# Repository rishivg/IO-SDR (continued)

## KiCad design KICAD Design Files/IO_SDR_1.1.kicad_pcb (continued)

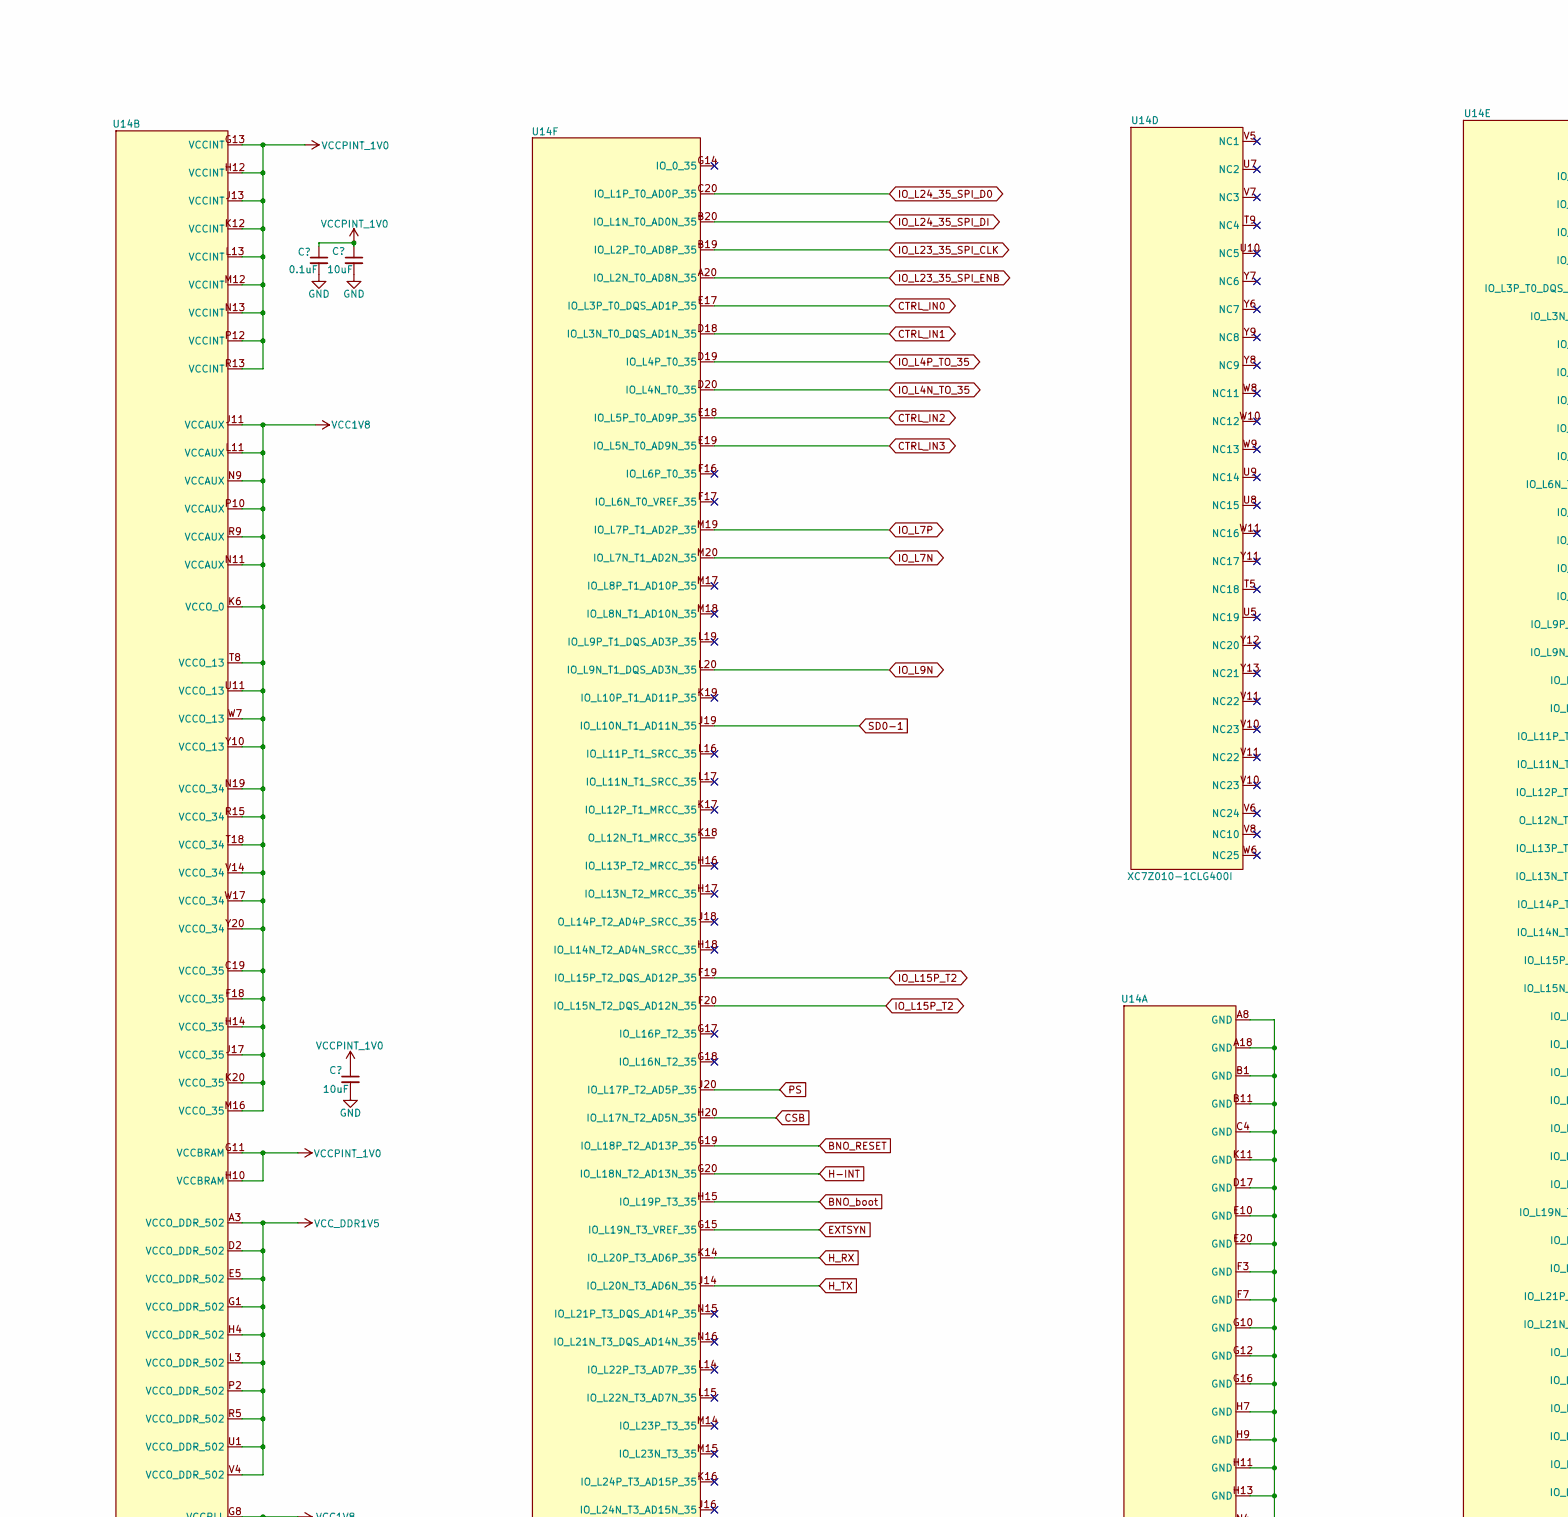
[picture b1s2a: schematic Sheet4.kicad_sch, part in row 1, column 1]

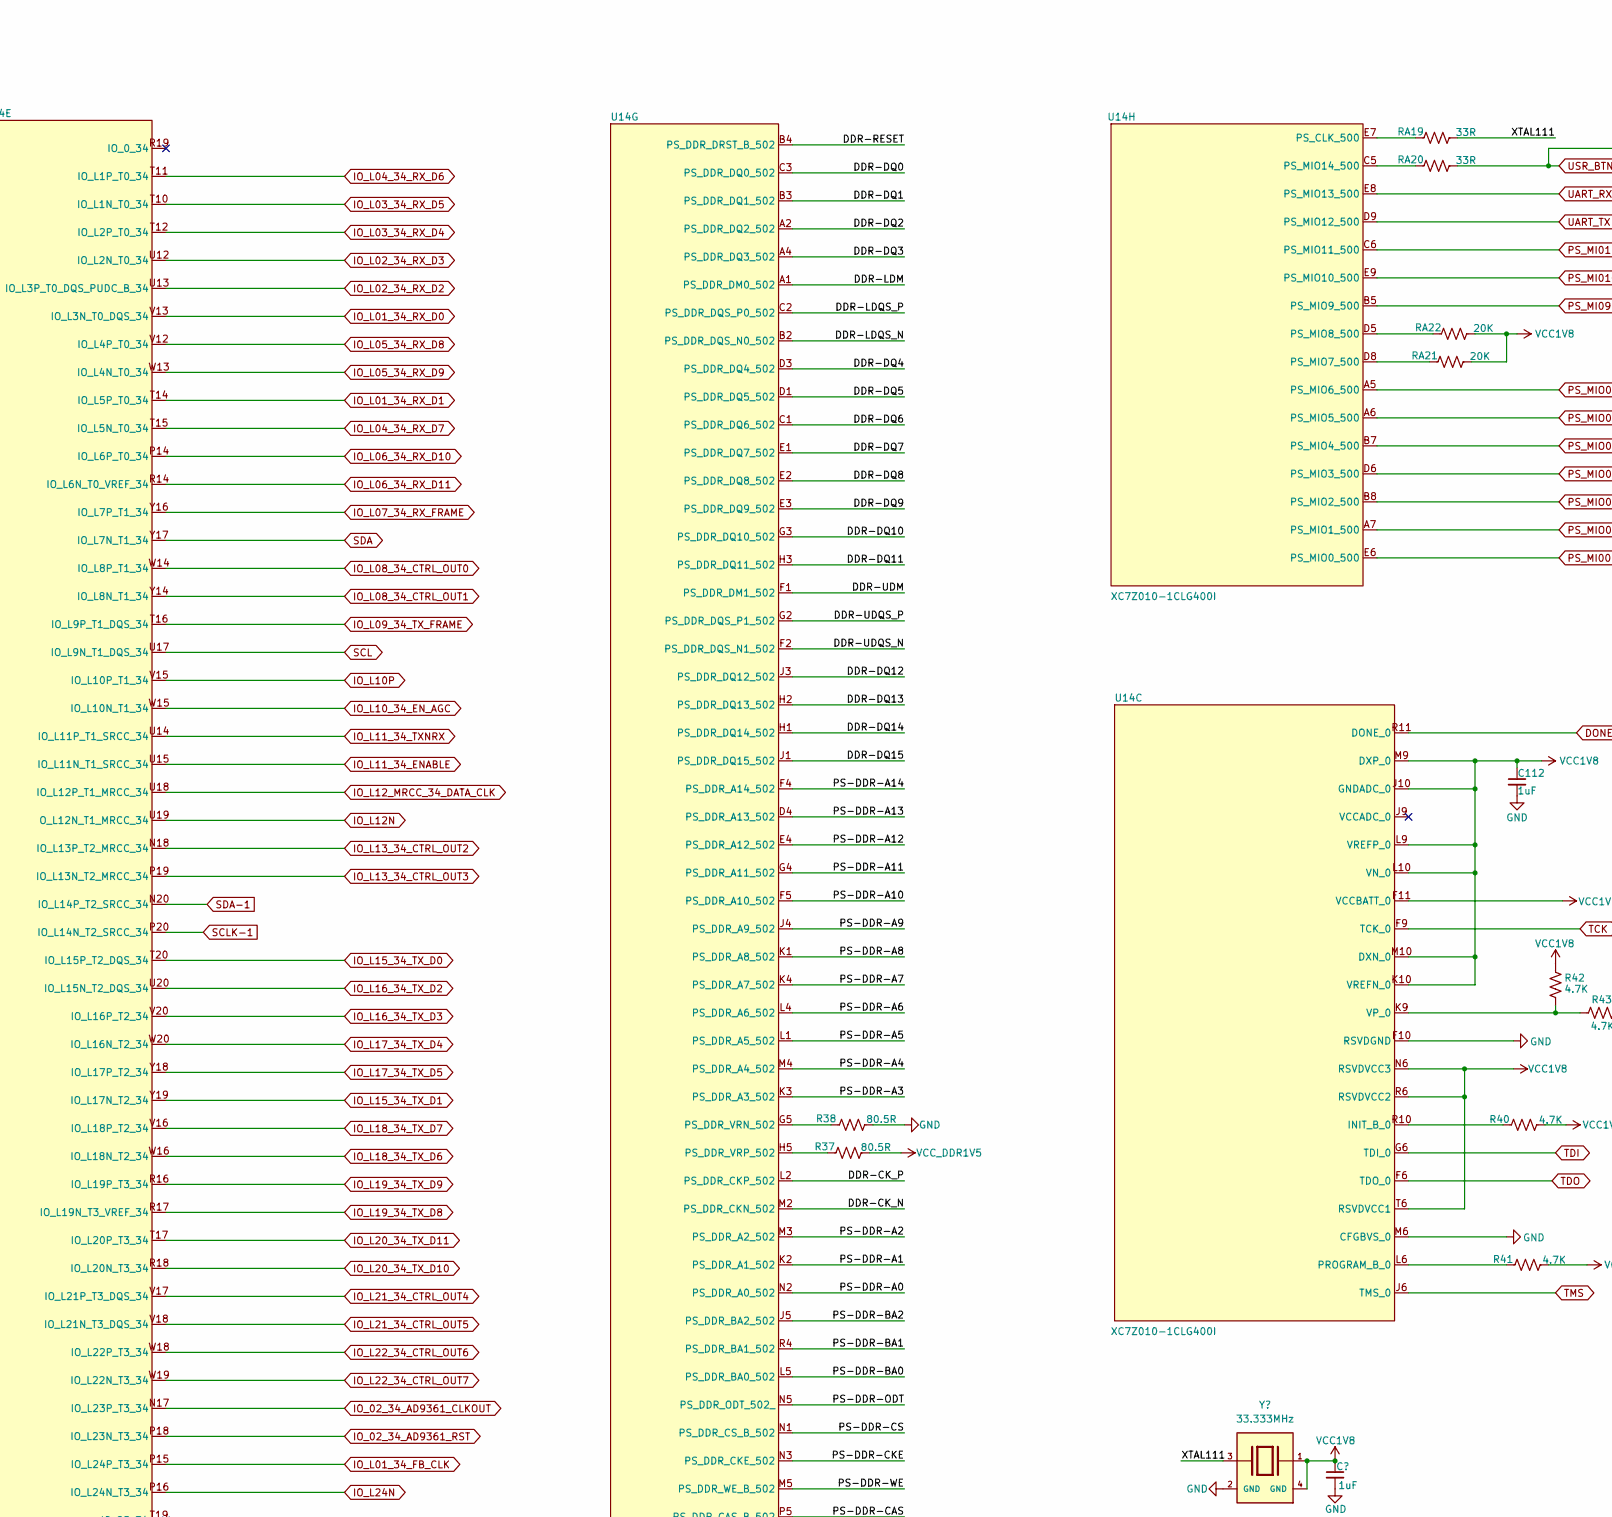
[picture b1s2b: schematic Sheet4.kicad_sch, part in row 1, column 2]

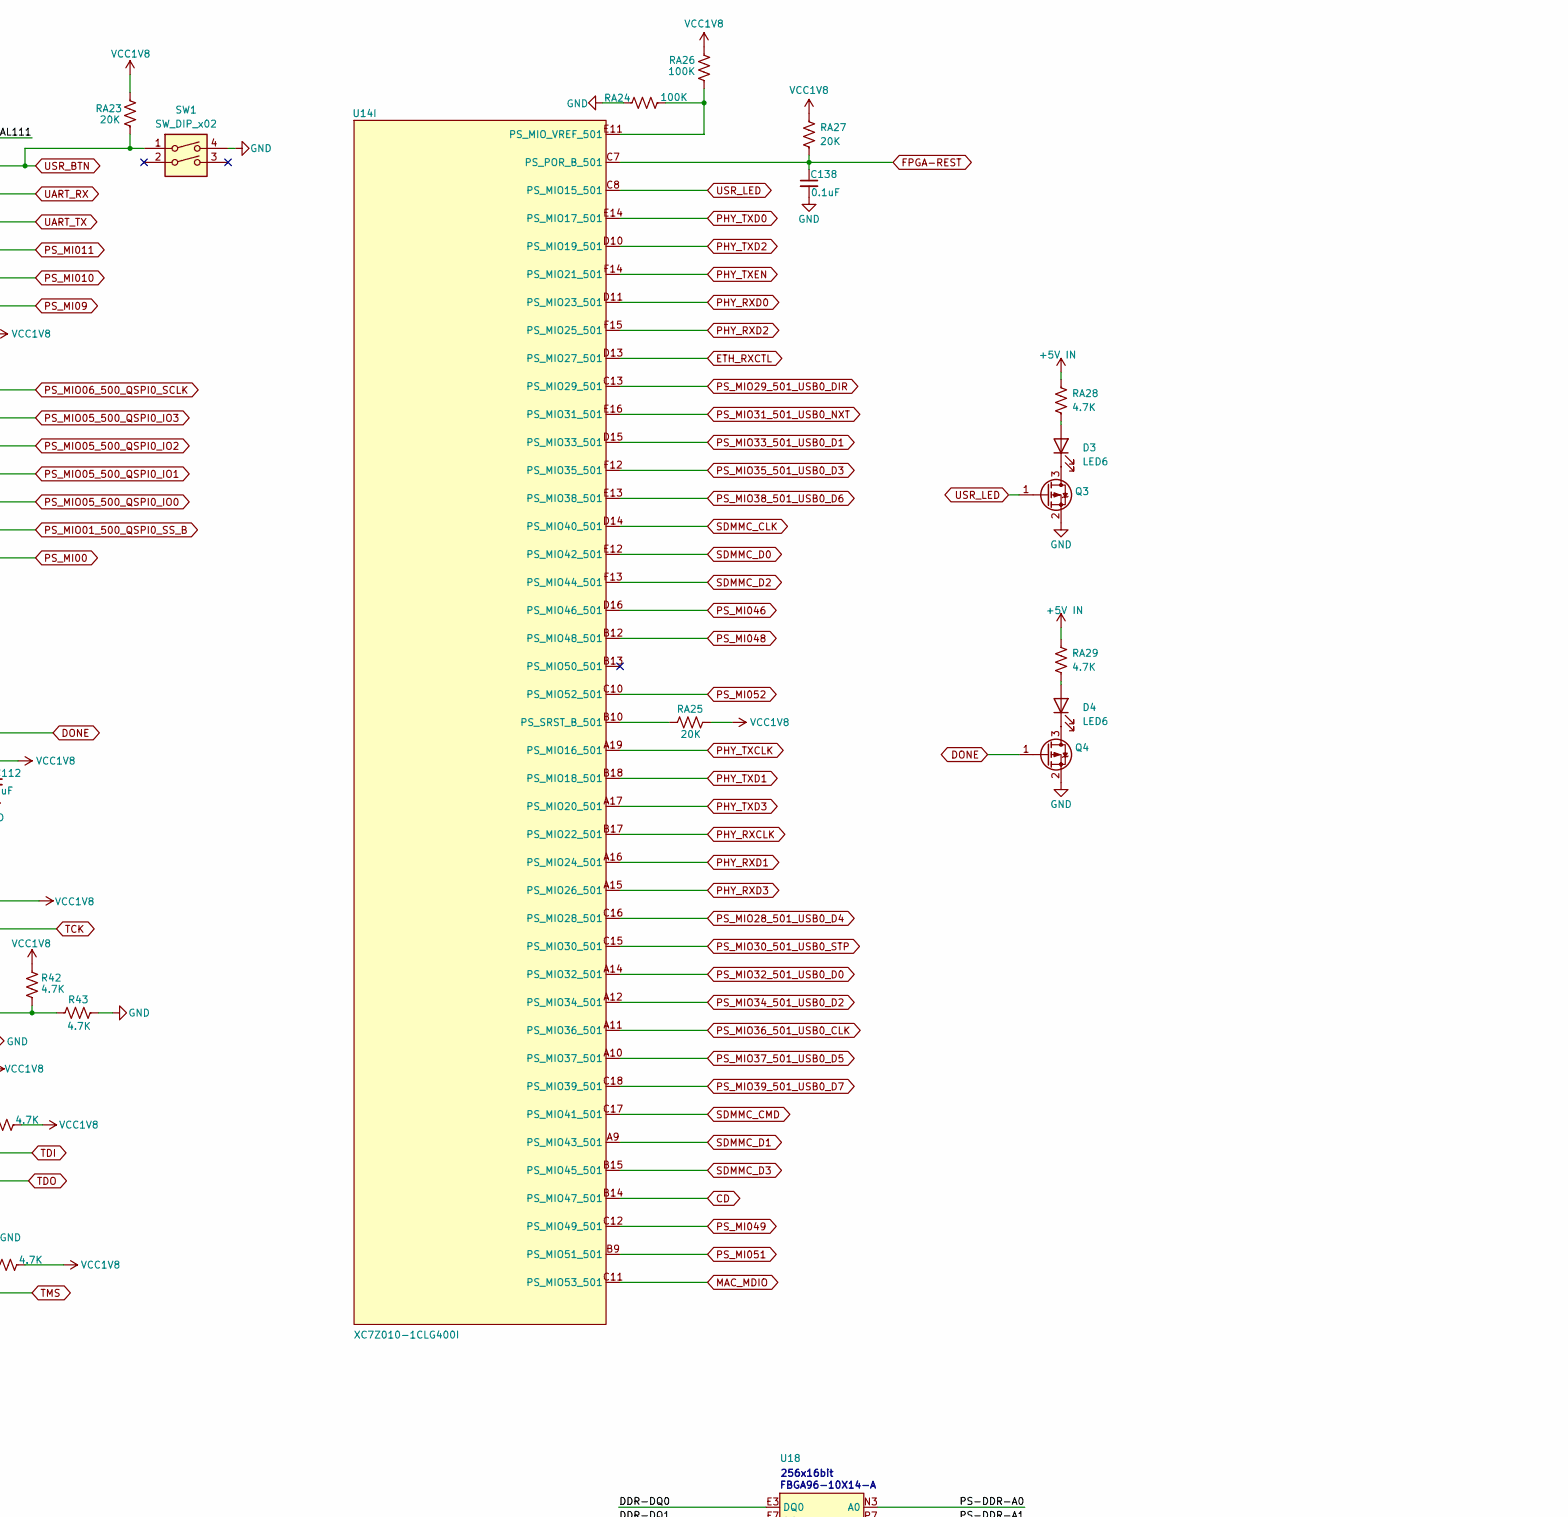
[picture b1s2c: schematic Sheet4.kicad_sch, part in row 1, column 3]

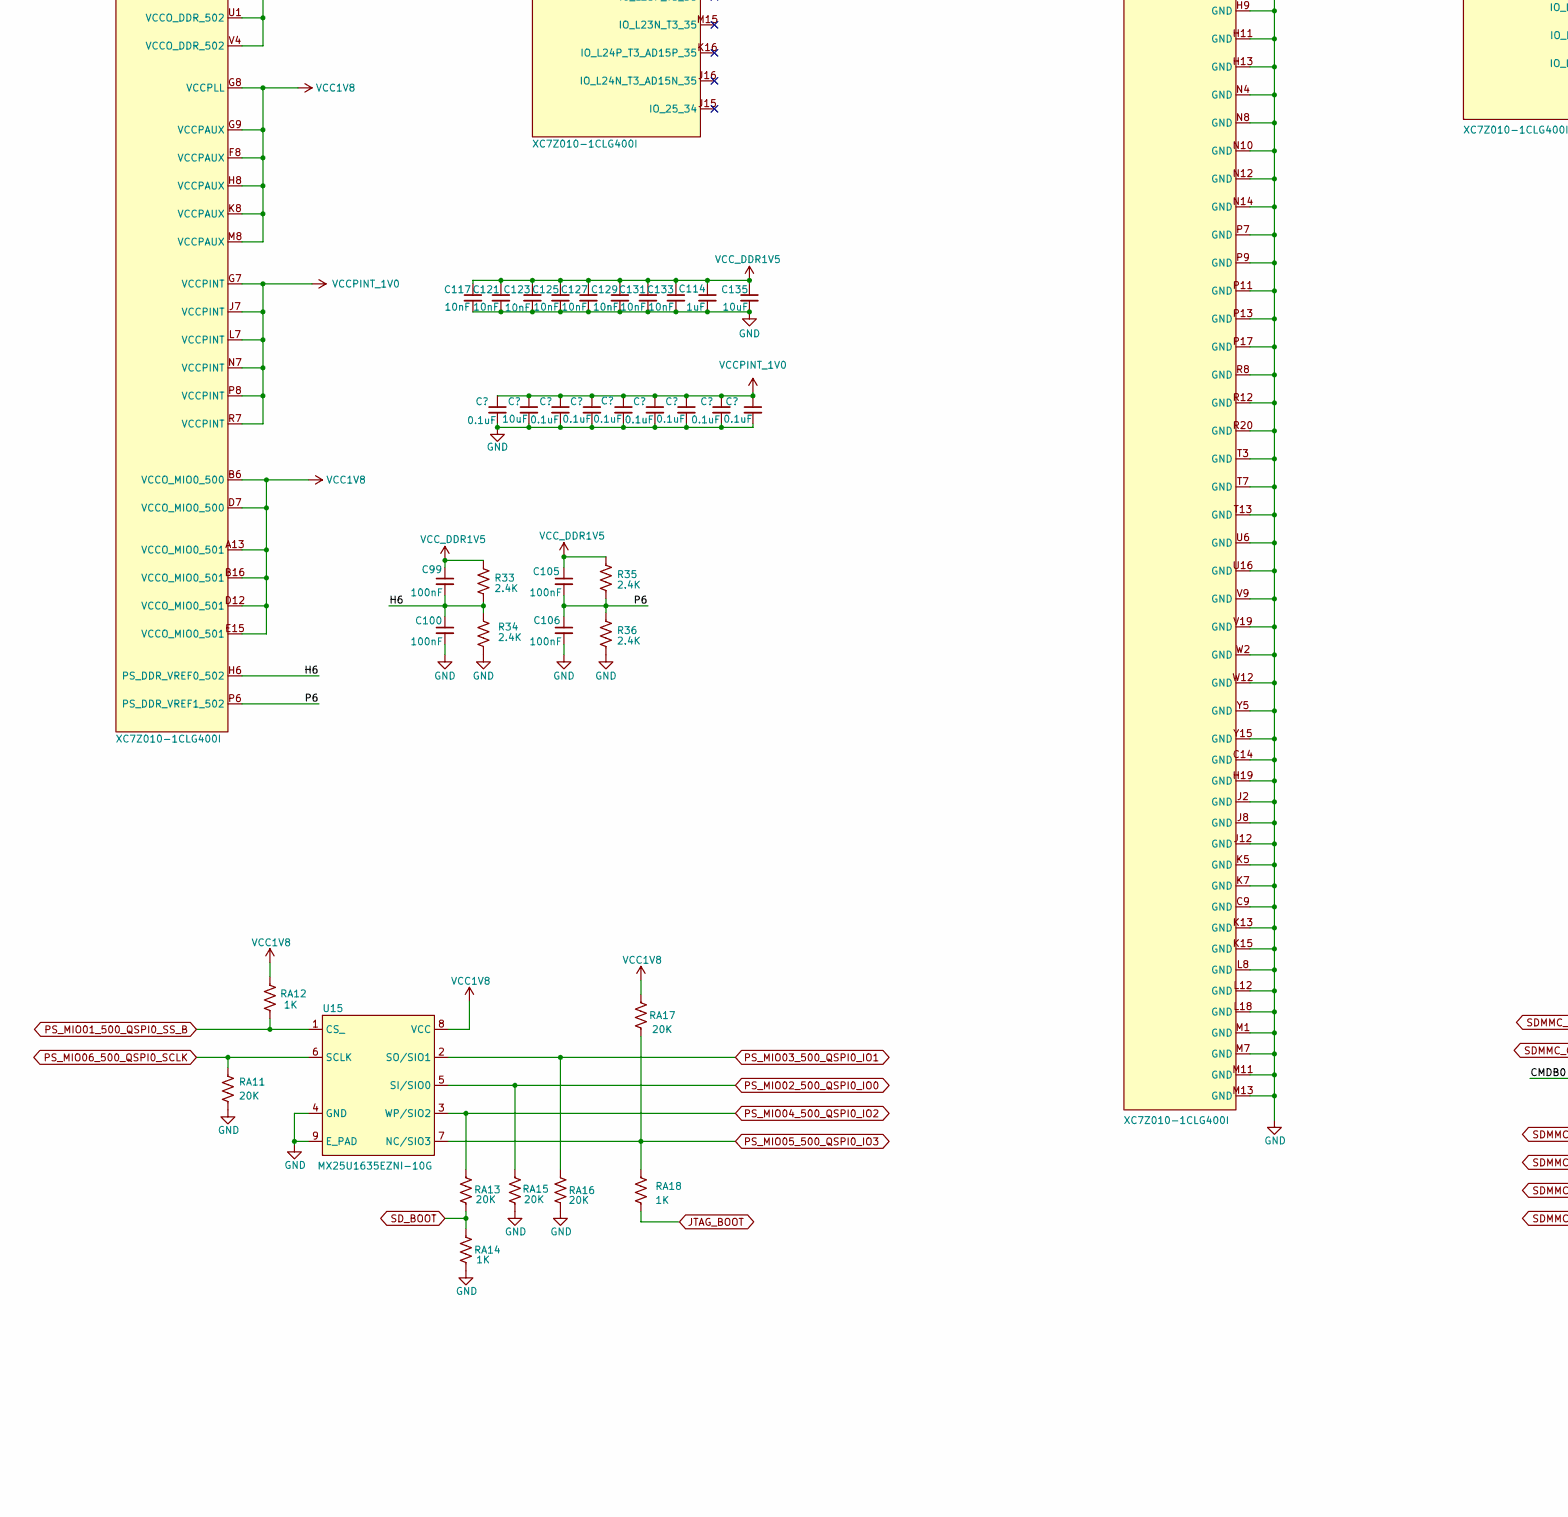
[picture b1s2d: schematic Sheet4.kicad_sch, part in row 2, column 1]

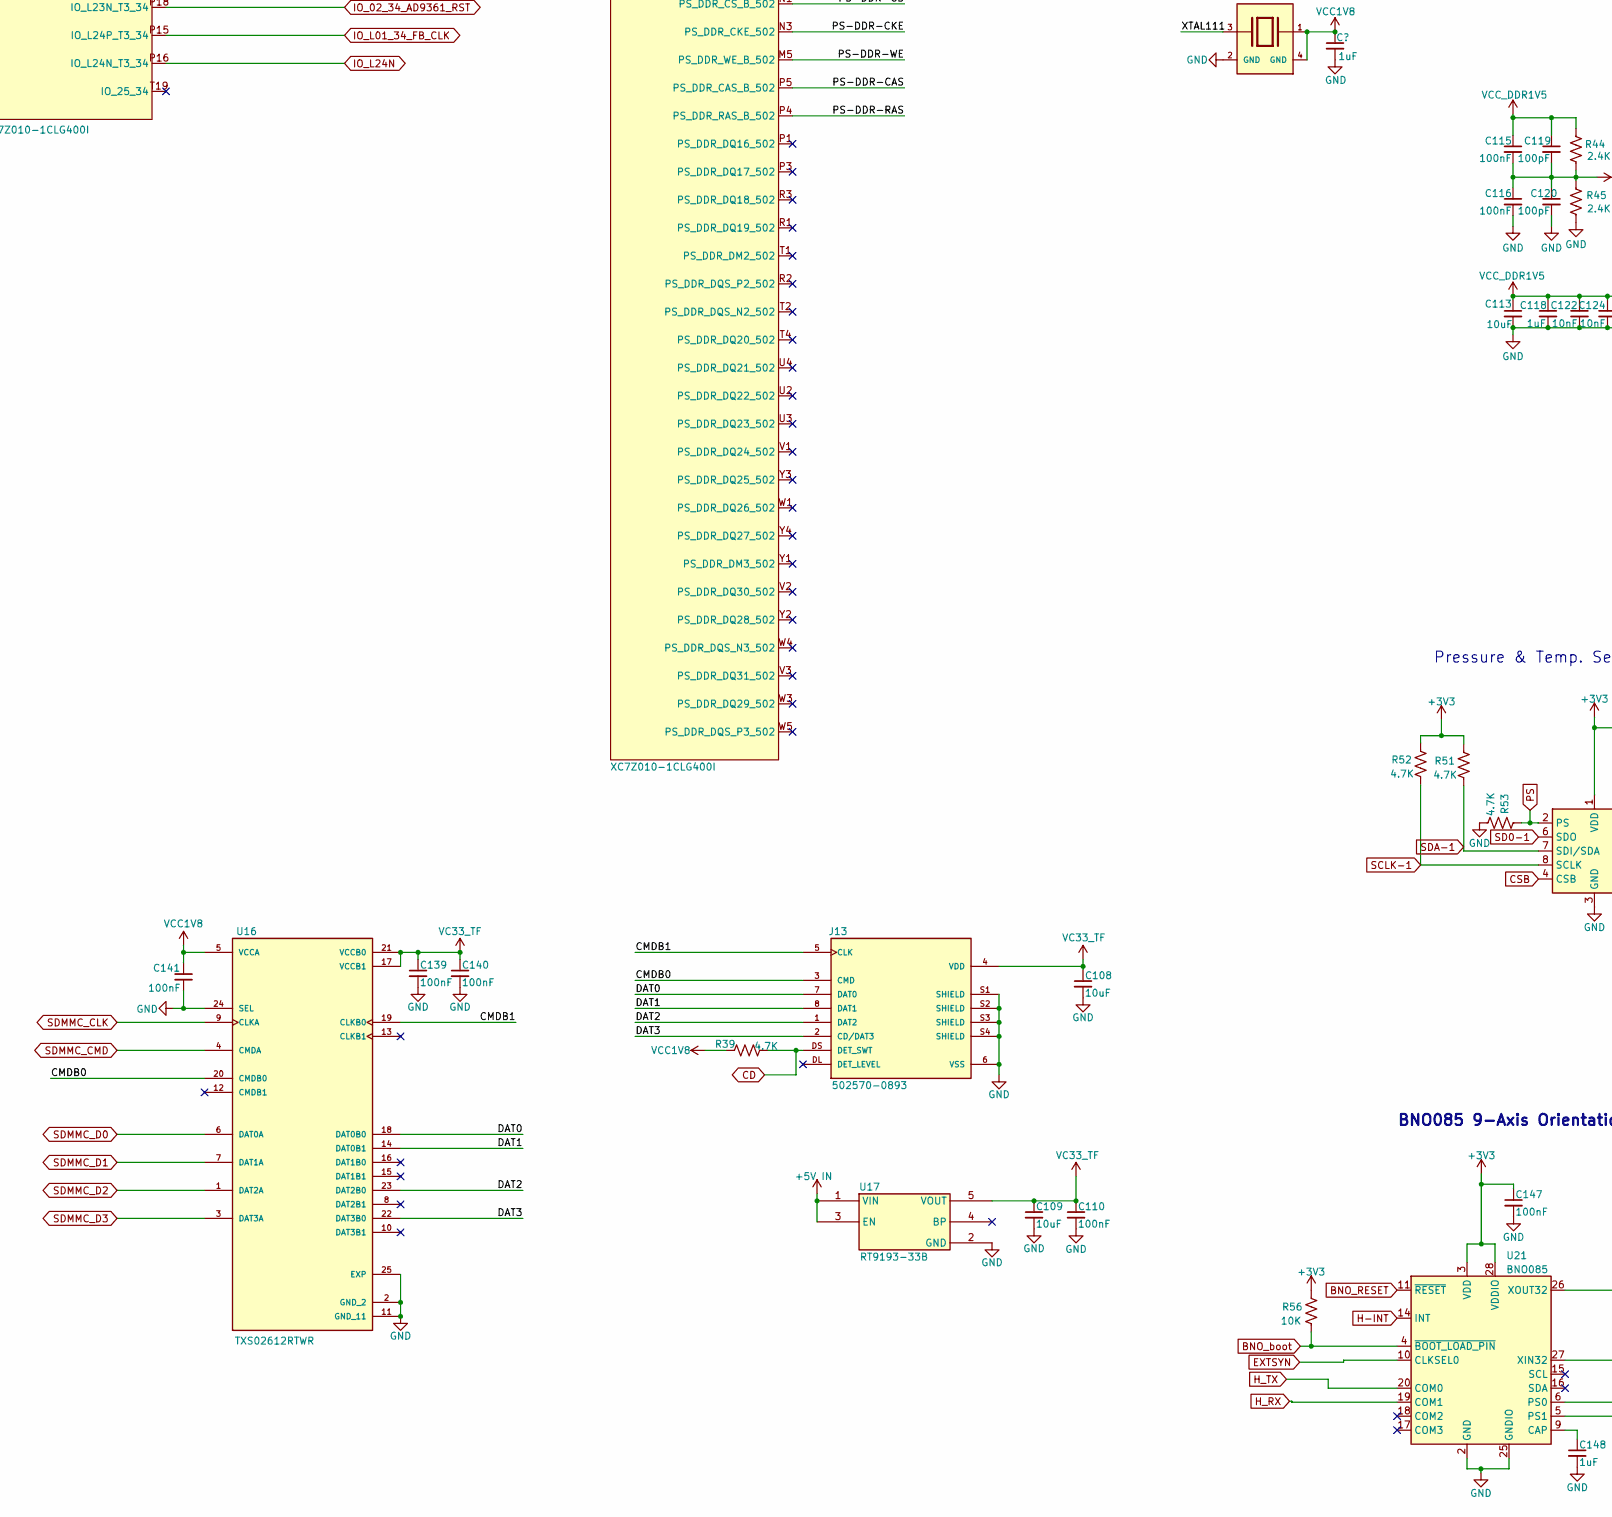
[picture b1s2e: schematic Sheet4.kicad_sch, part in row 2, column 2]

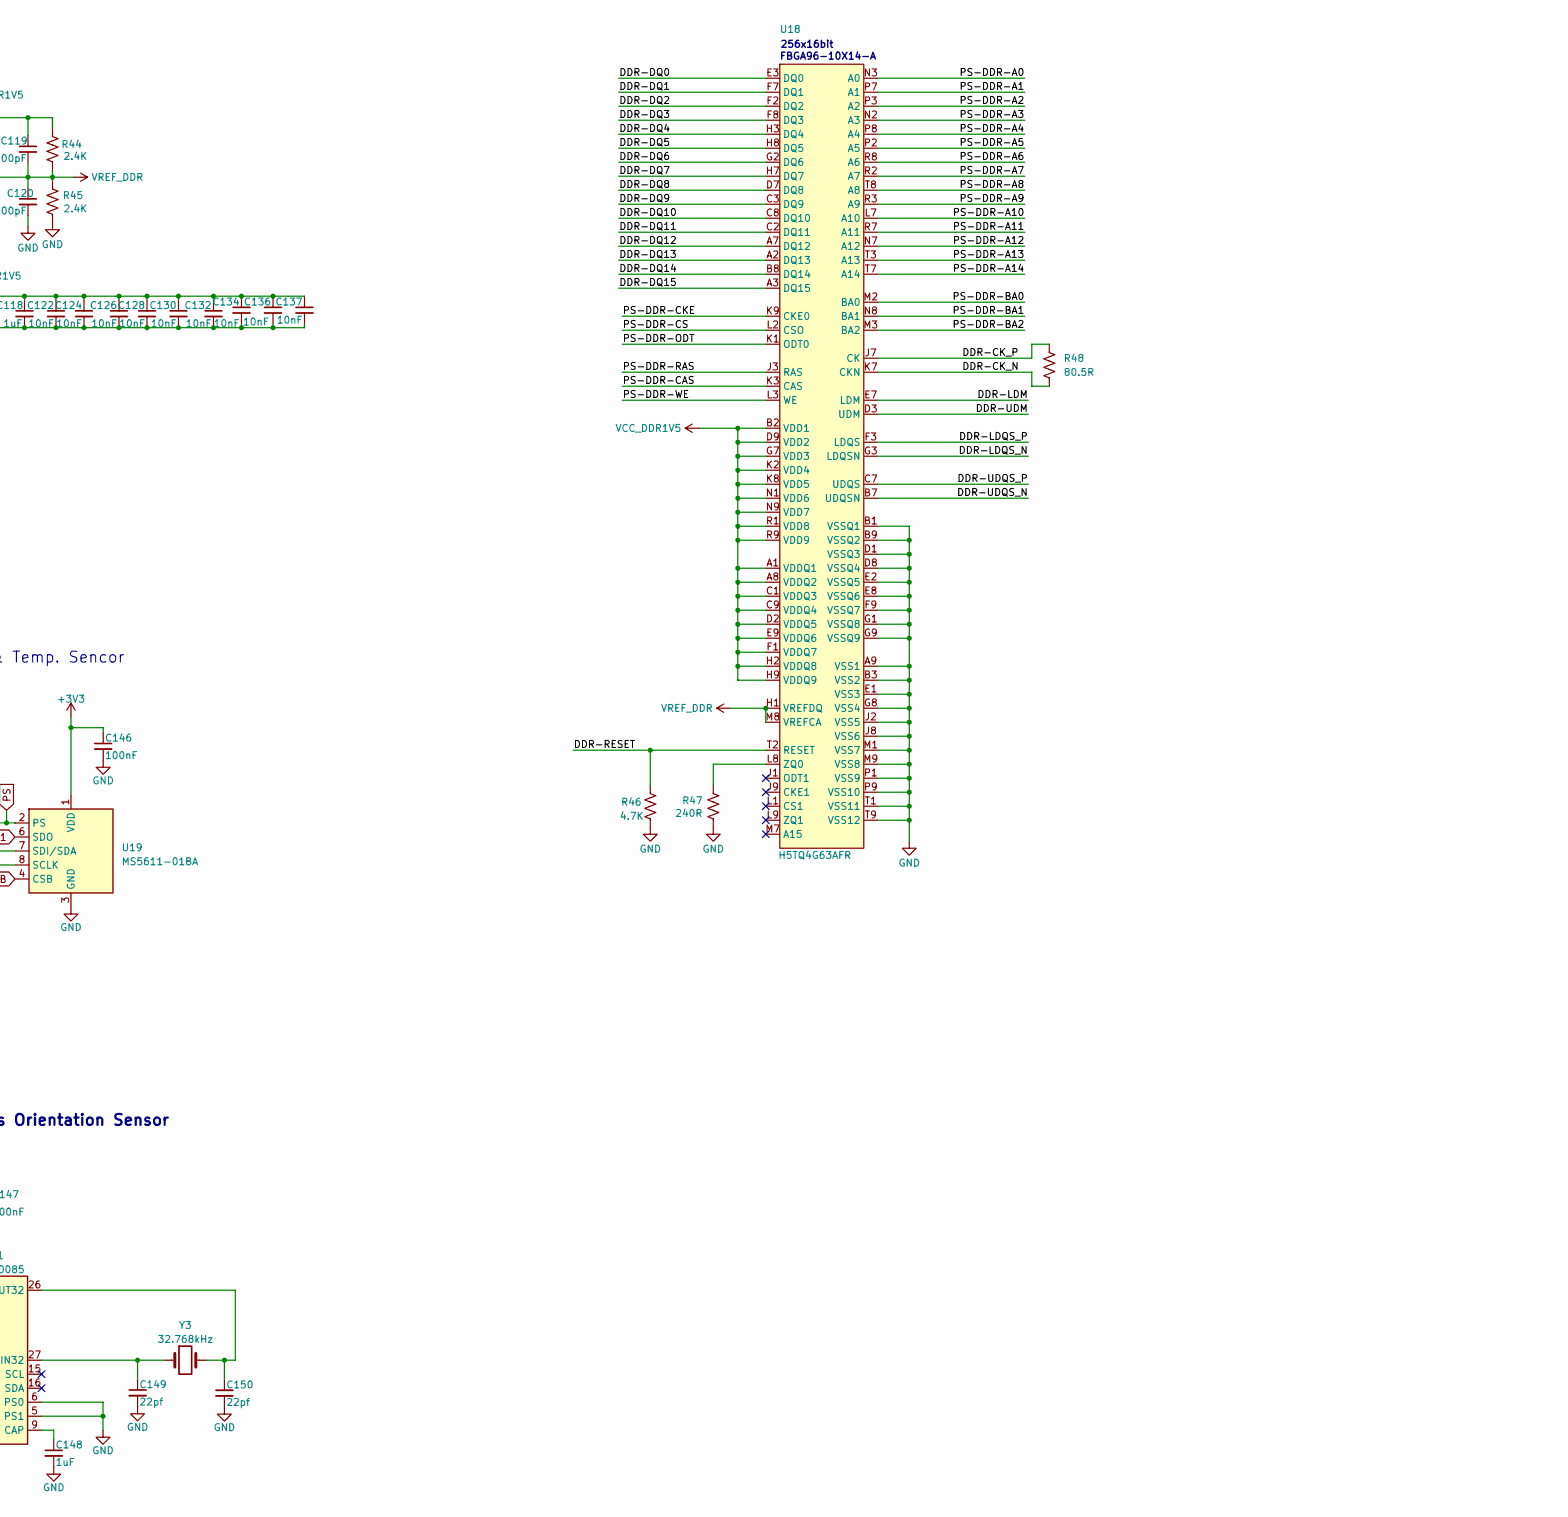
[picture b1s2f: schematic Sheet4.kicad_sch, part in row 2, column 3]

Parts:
C92, C93, C97, C98, C101, C102, C103, C104, C107, C138: 0.1uF; C_0402_1005Metric_Pad0.74x0.62mm_HandSolder
C94, C95, C96, C113, C135: 10uF; C_0402_1005Metric_Pad0.74x0.62mm_HandSolder
C99, C100, C105, C106, C110, C115, C116, C139, C140, C141, C146, C147: 100nF; C_0402_1005Metric_Pad0.74x0.62mm_HandSolder
C108, C109: 10uF; C_0805_2012Metric_Pad1.18x1.45mm_HandSolder
C111, C112, C114, C118, C148: 1uF; C_0402_1005Metric_Pad0.74x0.62mm_HandSolder
C117, C121, C122, C123, C124, C125, C126, C127, C128, C129, C130, C131, C132, C133, C134, C136, C137: 10nF; C_0402_1005Metric_Pad0.74x0.62mm_HandSolder
C119, C120: 100pF; C_0402_1005Metric_Pad0.74x0.62mm_HandSolder
C149, C150: 22pf; C_0402_1005Metric_Pad0.74x0.62mm_HandSolder
CY2: 33.333MHz; XTAL_ABM8AIG-25.000MHZ-12-2Z-T3; PARTREV 43629
D3, D4: LED6; LED_0603_1608Metric_Pad1.05x0.95mm_HandSolder
J13: 502570-0893; MOLEX_502570-0893
Q3, Q4: SOT23 MOSFET FOOT PRINT
R33, R34, R35, R36, R44, R45: 2.4K; R_0402_1005Metric_Pad0.72x0.64mm_HandSolder
R37, R38, R48: 80.5R; R_0402_1005Metric_Pad0.72x0.64mm_HandSolder
R39, R40, R41, R42, R43, R46, R51, R52, R53: 4.7K; R_0402_1005Metric_Pad0.72x0.64mm_HandSolder
R47: 240R; R_0402_1005Metric_Pad0.72x0.64mm_HandSolder
R56: 10K; R_0402_1005Metric_Pad0.72x0.64mm_HandSolder
RA11, RA13, RA15, RA16, RA17, RA21, RA22, RA23, RA25, RA27: 20K; R_0402_1005Metric_Pad0.72x0.64mm_HandSolder
RA12, RA14, RA18: 1K; R_0402_1005Metric_Pad0.72x0.64mm_HandSolder
RA19, RA20: 33R; R_0402_1005Metric_Pad0.72x0.64mm_HandSolder
RA24, RA26: 100K; R_0402_1005Metric_Pad0.72x0.64mm_HandSolder
RA28, RA29: 4.7K; R_0402_1005Metric_Pad0.72x0.64mm_HandSolder
SW1: SW_DIP_x02; SW_DIP_SPSTx02_Slide_6.7x6.64mm_W6.73mm_P2.54mm_LowProfile_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
U14: XC7Z010-1CLG400I
U15: MX25U1635EZNI-10G
U16: TXS02612RTWR; PARTREV 4219135/B 11/2016
U17: RT9193-33B
U18: H5TQ4G63AFR
U19: MS5611-01BA; LGA-8_3x5mm_P1.25mm
U21: BNO085; IC_BNO080
Y3: 32.768kHz; Crystal_SMD_Qantek_QC5CB-2Pin_5x3.2mm

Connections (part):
+1V0: C92.1, C93.1, C94.1, C95.1, C96.1, C97.1, C98.1, C101.1, C102.1, C103.1, C104.1, C107.1, U14.G7 (VCCPINT), U14.G11 (VCCBRAM), U14.G13 (VCCINT), U14.H10 (VCCBRAM), U14.H12 (VCCINT), U14.J7 (VCCPINT), U14.J13 (VCCINT), U14.K12 (VCCINT), U14.L7 (VCCPINT), U14.L13 (VCCINT), U14.M12 (VCCINT), U14.N7 (VCCPINT), U14.N13 (VCCINT), U14.P8 (VCCPINT), U14.P12 (VCCINT), U14.R7 (VCCPINT), U14.R13 (VCCINT); also elsewhere on the board
+1V5: C99.1, C105.1, C113.1, C114.1, C115.1, C117.1, C118.1, C119.1, C121.1, C122.1, C123.1, C124.1, C125.1, C126.1, C127.1, C128.1, C129.1, C130.1, C131.1, C132.1, C133.1, C134.1, C135.1, C136.1, C137.1, R33.1, R35.1, R37.2, R44.1, U14.A3 (VCCO_DDR_502), U14.D2 (VCCO_DDR_502), U14.E5 (VCCO_DDR_502), U14.G1 (VCCO_DDR_502), U14.H4 (VCCO_DDR_502), U14.L3 (VCCO_DDR_502), U14.P2 (VCCO_DDR_502), U14.R5 (VCCO_DDR_502), U14.U1 (VCCO_DDR_502), U14.V4 (VCCO_DDR_502), U18.A1 (VDDQ1), U18.A8 (VDDQ2), U18.B2 (VDD1), U18.C1 (VDDQ3), U18.C9 (VDDQ4), U18.D2 (VDDQ5), U18.D9 (VDD2), U18.E9 (VDDQ6), U18.F1 (VDDQ7), U18.G7 (VDD3), U18.H2 (VDDQ8), U18.H9 (VDDQ9), U18.K2 (VDD4), U18.K8 (VDD5), U18.N1 (VDD6), U18.N9 (VDD7), U18.R1 (VDD8), U18.R9 (VDD9); also elsewhere on the board
+1V8: C111.1, C112.1, C141.1, CY2.1, CY2.4 (GND), R39.1, R40.2, R41.2, R42.1, RA12.1, RA17.1, RA21.2, RA22.2, RA23.1, RA25.2, RA26.1, RA27.1, U14.A13 (VCCO_MIO0_501), U14.B6 (VCCO_MIO0_500), U14.B16 (VCCO_MIO0_501), U14.C19 (VCCO_35), U14.D7 (VCCO_MIO0_500), U14.D12 (VCCO_MIO0_501), U14.E15 (VCCO_MIO0_501), U14.F8 (VCCPAUX), U14.F11 (VCCBATT_0), U14.F18 (VCCO_35), U14.G8 (VCCPLL), U14.G9 (VCCPAUX), U14.H8 (VCCPAUX), U14.H14 (VCCO_35), U14.J10 (GNDADC_0), U14.J11 (VCCAUX), U14.J17 (VCCO_35), U14.K6 (VCCO_0), U14.K8 (VCCPAUX), U14.K10 (VREFN_0), U14.K20 (VCCO_35), U14.L9 (VREFP_0), U14.L10 (VN_0), U14.L11 (VCCAUX), U14.M8 (VCCPAUX), U14.M9 (DXP_0), U14.M10 (DXN_0), U14.M16 (VCCO_35), U14.N6 (RSVDVCC3), U14.N9 (VCCAUX), U14.N11 (VCCAUX), U14.N19 (VCCO_34), U14.P10 (VCCAUX), U14.R6 (RSVDVCC2), U14.R9 (VCCAUX), U14.R15 (VCCO_34), U14.T6 (RSVDVCC1), U14.T8 (VCCO_13), U14.T18 (VCCO_34), U14.U11 (VCCO_13), U14.V14 (VCCO_34), U14.W7 (VCCO_13), U14.W17 (VCCO_34), U14.Y10 (VCCO_13), U14.Y20 (VCCO_34), U15.8 (VCC), U16.5 (VCCA); also elsewhere on the board
+15V: C115.2, C116.1, C119.2, C120.1, R44.2, R45.1, U18.H1 (VREFDQ), U18.M8 (VREFCA)
/Sheet4/CMDB0: J13.3 (CMD), U16.20 (CMDB0)
/Sheet4/CMDB1: J13.5 (CLK), U16.19 (CLKB0)
/Sheet4/DAT0: J13.7 (DAT0), U16.18 (DAT0B0)
/Sheet4/DAT1: J13.8 (DAT1), U16.14 (DAT0B1)
/Sheet4/DAT2: J13.1 (DAT2), U16.23 (DAT2B0)
/Sheet4/DAT3: J13.2 (CD/DAT3), U16.22 (DAT3B0)
/Sheet4/DDR-CK_N: R48.2, U14.M2 (PS_DDR_CKN_502), U18.K7 (CKN)
/Sheet4/DDR-CK_P: R48.1, U14.L2 (PS_DDR_CKP_502), U18.J7 (CK)
/Sheet4/DDR-DQ0: U14.C3 (PS_DDR_DQ0_502), U18.E3 (DQ0)
/Sheet4/DDR-DQ1: U14.B3 (PS_DDR_DQ1_502), U18.F7 (DQ1)
/Sheet4/DDR-DQ2: U14.A2 (PS_DDR_DQ2_502), U18.F2 (DQ2)
/Sheet4/DDR-DQ3: U14.A4 (PS_DDR_DQ3_502), U18.F8 (DQ3)
/Sheet4/DDR-DQ4: U14.D3 (PS_DDR_DQ4_502), U18.H3 (DQ4)
/Sheet4/DDR-DQ5: U14.D1 (PS_DDR_DQ5_502), U18.H8 (DQ5)
/Sheet4/DDR-DQ6: U14.C1 (PS_DDR_DQ6_502), U18.G2 (DQ6)
/Sheet4/DDR-DQ7: U14.E1 (PS_DDR_DQ7_502), U18.H7 (DQ7)
/Sheet4/DDR-DQ8: U14.E2 (PS_DDR_DQ8_502), U18.D7 (DQ8)
/Sheet4/DDR-DQ9: U14.E3 (PS_DDR_DQ9_502), U18.C3 (DQ9)
/Sheet4/DDR-DQ10: U14.G3 (PS_DDR_DQ10_502), U18.C8 (DQ10)
/Sheet4/DDR-DQ11: U14.H3 (PS_DDR_DQ11_502), U18.C2 (DQ11)
/Sheet4/DDR-DQ12: U14.J3 (PS_DDR_DQ12_502), U18.A7 (DQ12)
/Sheet4/DDR-DQ13: U14.H2 (PS_DDR_DQ13_502), U18.A2 (DQ13)
/Sheet4/DDR-DQ14: U14.H1 (PS_DDR_DQ14_502), U18.B8 (DQ14)
/Sheet4/DDR-DQ15: U14.J1 (PS_DDR_DQ15_502), U18.A3 (DQ15)
/Sheet4/DDR-LDM: U14.A1 (PS_DDR_DM0_502), U18.E7 (LDM)
/Sheet4/DDR-LDQS_N: U14.B2 (PS_DDR_DQS_N0_502), U18.G3 (LDQSN)
/Sheet4/DDR-LDQS_P: U14.C2 (PS_DDR_DQS_P0_502), U18.F3 (LDQS)
/Sheet4/DDR-RESET: R46.1, U14.B4 (PS_DDR_DRST_B_502), U18.T2 (RESET)
/Sheet4/DDR-UDM: U14.F1 (PS_DDR_DM1_502), U18.D3 (UDM)
/Sheet4/DDR-UDQS_N: U14.F2 (PS_DDR_DQS_N1_502), U18.B7 (UDQSN)
/Sheet4/DDR-UDQS_P: U14.G2 (PS_DDR_DQS_P1_502), U18.C7 (UDQS)
/Sheet4/H6: C99.2, C100.1, R33.2, R34.1, U14.H6 (PS_DDR_VREF0_502)
/Sheet4/P6: C105.2, C106.1, R35.2, R36.1, U14.P6 (PS_DDR_VREF1_502)
/Sheet4/PS-DDR-A0: U14.N2 (PS_DDR_A0_502), U18.N3 (A0)
/Sheet4/PS-DDR-A1: U14.K2 (PS_DDR_A1_502), U18.P7 (A1)
/Sheet4/PS-DDR-A2: U14.M3 (PS_DDR_A2_502), U18.P3 (A2)
/Sheet4/PS-DDR-A3: U14.K3 (PS_DDR_A3_502), U18.N2 (A3)
/Sheet4/PS-DDR-A4: U14.M4 (PS_DDR_A4_502), U18.P8 (A4)
/Sheet4/PS-DDR-A5: U14.L1 (PS_DDR_A5_502), U18.P2 (A5)
/Sheet4/PS-DDR-A6: U14.L4 (PS_DDR_A6_502), U18.R8 (A6)
/Sheet4/PS-DDR-A7: U14.K4 (PS_DDR_A7_502), U18.R2 (A7)
/Sheet4/PS-DDR-A8: U14.K1 (PS_DDR_A8_502), U18.T8 (A8)
/Sheet4/PS-DDR-A9: U14.J4 (PS_DDR_A9_502), U18.R3 (A9)
/Sheet4/PS-DDR-A10: U14.F5 (PS_DDR_A10_502), U18.L7 (A10)
/Sheet4/PS-DDR-A11: U14.G4 (PS_DDR_A11_502), U18.R7 (A11)
/Sheet4/PS-DDR-A12: U14.E4 (PS_DDR_A12_502), U18.N7 (A12)
/Sheet4/PS-DDR-A13: U14.D4 (PS_DDR_A13_502), U18.T3 (A13)
/Sheet4/PS-DDR-A14: U14.F4 (PS_DDR_A14_502), U18.T7 (A14)
/Sheet4/PS-DDR-BA0: U14.L5 (PS_DDR_BA0_502), U18.M2 (BA0)
/Sheet4/PS-DDR-BA1: U14.R4 (PS_DDR_BA1_502), U18.N8 (BA1)
/Sheet4/PS-DDR-BA2: U14.J5 (PS_DDR_BA2_502), U18.M3 (BA2)
/Sheet4/PS-DDR-CAS: U14.P5 (PS_DDR_CAS_B_502), U18.K3 (CAS)
/Sheet4/PS-DDR-CKE: U14.N3 (PS_DDR_CKE_502), U18.K9 (CKE0)
/Sheet4/PS-DDR-CS: U14.N1 (PS_DDR_CS_B_502), U18.L2 (CSO)
/Sheet4/PS-DDR-ODT: U14.N5 (PS_DDR_ODT_502_), U18.K1 (ODT0)
/Sheet4/PS-DDR-RAS: U14.P4 (PS_DDR_RAS_B_502), U18.J3 (RAS)
/Sheet4/PS-DDR-WE: U14.M5 (PS_DDR_WE_B_502), U18.L3 (WE)
/Sheet4/XTAL111: CY2.3, RA19.2
BNO_RESET: U14.G19 (IO_L18P_T2_AD13P_35), U21.11 (~RESET)
BNO_boot: R56.2, U14.H15 (IO_L19P_T3_35), U21.4 (~BOOT_LOAD_PIN)
CD: J13.DS (DET_SWT), R39.2, U14.B14 (PS_MIO47_501)
CSB: U14.H20 (IO_L17N_T2_AD5N_35), U19.4 (CSB), U19.5 (CSB)
CTRL_IN0: U14.E17 (IO_L3P_T0_DQS_AD1P_35); also elsewhere on the board
CTRL_IN1: U14.D18 (IO_L3N_T0_DQS_AD1N_35); also elsewhere on the board
CTRL_IN2: U14.E18 (IO_L5P_T0_AD9P_35); also elsewhere on the board
CTRL_IN3: U14.E19 (IO_L5N_T0_AD9N_35); also elsewhere on the board
DONE: Q4.1 (G), U14.R11 (DONE_0); also elsewhere on the board
ETH_RXCTL: U14.D13 (PS_MIO27_501); also elsewhere on the board
EXTSYN: U14.G15 (IO_L19N_T3_VREF_35), U21.10 (CLKSEL0)
FPGA-REST: C138.1, RA27.2, U14.C7 (PS_POR_B_501)
GND: C92.2, C93.2, C94.2, C95.2, C96.2, C97.2, C98.2, C100.2, C101.2, C102.2, C103.2, C104.2, C106.2, C107.2, C108.2, C109.2, C110.2, C111.2, C112.2, C113.2, C114.2, C116.2, C117.2, C118.2, C120.2, C121.2, C122.2, C123.2, C124.2, C125.2, C126.2, C127.2, C128.2, C129.2, C130.2, C131.2, C132.2, C133.2, C134.2, C135.2, C136.2, C137.2, C138.2, C139.2, C140.2, C141.2, C146.2, C147.2, C148.2, C149.2, C150.2, CY2.2 (GND), J13.6 (VSS), J13.S1 (SHIELD), J13.S2 (SHIELD), J13.S3 (SHIELD), J13.S4 (SHIELD), Q3.2 (S), Q4.2 (S), R34.2, R36.2, R38.2, R43.2, R45.2, R46.2, R47.2, R53.2, RA11.2, RA14.2, RA15.2, RA16.2, RA24.1, SW1.4, U14.A8 (GND), U14.A18 (GND), U14.B1 (GND), U14.B11 (GND), U14.C4 (GND), U14.C9 (GND), U14.C14 (GND), U14.D17 (GND), U14.E10 (GND), U14.E20 (GND)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; also elsewhere on the board
H-INT: U14.G20 (IO_L18N_T2_AD13N_35), U21.14 (INT)
H_RX: U14.K14 (IO_L20P_T3_AD6P_35), U21.19 (COM1)
H_TX: U14.J14 (IO_L20N_T3_AD6N_35), U21.20 (COM0)
IO_02_34_AD9361_CLKOUT: U14.N17 (IO_L23P_T3_34); also elsewhere on the board
IO_02_34_AD9361_RST: U14.P18 (IO_L23N_T3_34); also elsewhere on the board
IO_L01_34_FB_CLK: U14.P15 (IO_L24P_T3_34); also elsewhere on the board
IO_L01_34_RX_D0: U14.V13 (IO_L3N_T0_DQS_34); also elsewhere on the board
IO_L01_34_RX_D1: U14.T14 (IO_L5P_T0_34); also elsewhere on the board
IO_L02_34_RX_D2: U14.U13 (IO_L3P_T0_DQS_PUDC_B_34); also elsewhere on the board
IO_L02_34_RX_D3: U14.U12 (IO_L2N_T0_34); also elsewhere on the board
IO_L03_34_RX_D4: U14.T12 (IO_L2P_T0_34); also elsewhere on the board
IO_L03_34_RX_D5: U14.T10 (IO_L1N_T0_34); also elsewhere on the board
IO_L4N_TO_35: U14.D20 (IO_L4N_T0_35); also elsewhere on the board
IO_L4P_TO_35: U14.D19 (IO_L4P_T0_35); also elsewhere on the board
IO_L04_34_RX_D6: U14.T11 (IO_L1P_T0_34); also elsewhere on the board
IO_L04_34_RX_D7: U14.T15 (IO_L5N_T0_34); also elsewhere on the board
IO_L05_34_RX_D8: U14.V12 (IO_L4P_T0_34); also elsewhere on the board
IO_L05_34_RX_D9: U14.W13 (IO_L4N_T0_34); also elsewhere on the board
IO_L06_34_RX_D10: U14.P14 (IO_L6P_T0_34); also elsewhere on the board
IO_L06_34_RX_D11: U14.R14 (IO_L6N_T0_VREF_34); also elsewhere on the board
IO_L7N: U14.M20 (IO_L7N_T1_AD2N_35); also elsewhere on the board
IO_L7P: U14.M19 (IO_L7P_T1_AD2P_35); also elsewhere on the board
IO_L07_34_RX_FRAME: U14.Y16 (IO_L7P_T1_34); also elsewhere on the board
IO_L08_34_CTRL_OUT0: U14.W14 (IO_L8P_T1_34); also elsewhere on the board
IO_L08_34_CTRL_OUT1: U14.Y14 (IO_L8N_T1_34); also elsewhere on the board
IO_L9N: U14.L20 (IO_L9N_T1_DQS_AD3N_35); also elsewhere on the board
IO_L09_34_TX_FRAME: U14.T16 (IO_L9P_T1_DQS_34); also elsewhere on the board
IO_L10P: U14.V15 (IO_L10P_T1_34); also elsewhere on the board
IO_L10_34_EN_AGC: U14.W15 (IO_L10N_T1_34); also elsewhere on the board
IO_L11_34_ENABLE: U14.U15 (IO_L11N_T1_SRCC_34); also elsewhere on the board
IO_L11_34_TXNRX: U14.U14 (IO_L11P_T1_SRCC_34); also elsewhere on the board
IO_L12N: U14.U19 (O_L12N_T1_MRCC_34); also elsewhere on the board
IO_L12_MRCC_34_DATA_CLK: U14.U18 (IO_L12P_T1_MRCC_34); also elsewhere on the board
IO_L13_34_CTRL_OUT2: U14.N18 (IO_L13P_T2_MRCC_34)
IO_L13_34_CTRL_OUT3: U14.P19 (IO_L13N_T2_MRCC_34)
IO_L15P_T2: U14.F19 (IO_L15P_T2_DQS_AD12P_35), U14.F20 (IO_L15N_T2_DQS_AD12N_35); also elsewhere on the board
IO_L15_34_TX_D0: U14.T20 (IO_L15P_T2_DQS_34); also elsewhere on the board
IO_L15_34_TX_D1: U14.Y19 (IO_L17N_T2_34); also elsewhere on the board
IO_L16_34_TX_D2: U14.U20 (IO_L15N_T2_DQS_34); also elsewhere on the board
IO_L16_34_TX_D3: U14.V20 (IO_L16P_T2_34); also elsewhere on the board
IO_L17_34_TX_D4: U14.W20 (IO_L16N_T2_34); also elsewhere on the board
IO_L17_34_TX_D5: U14.Y18 (IO_L17P_T2_34); also elsewhere on the board
IO_L18_34_TX_D6: U14.W16 (IO_L18N_T2_34); also elsewhere on the board
IO_L18_34_TX_D7: U14.V16 (IO_L18P_T2_34); also elsewhere on the board
IO_L19_34_TX_D8: U14.R17 (IO_L19N_T3_VREF_34); also elsewhere on the board
IO_L19_34_TX_D9: U14.R16 (IO_L19P_T3_34); also elsewhere on the board
IO_L20_34_TX_D10: U14.R18 (IO_L20N_T3_34); also elsewhere on the board
IO_L20_34_TX_D11: U14.T17 (IO_L20P_T3_34); also elsewhere on the board
IO_L21_34_CTRL_OUT4: U14.V17 (IO_L21P_T3_DQS_34)
IO_L21_34_CTRL_OUT5: U14.V18 (IO_L21N_T3_DQS_34)
IO_L22_34_CTRL_OUT6: U14.W18 (IO_L22P_T3_34)
IO_L22_34_CTRL_OUT7: U14.W19 (IO_L22N_T3_34)
IO_L23_35_SPI_CLK: U14.B19 (IO_L2P_T0_AD8P_35); also elsewhere on the board
IO_L23_35_SPI_ENB: U14.A20 (IO_L2N_T0_AD8N_35); also elsewhere on the board
IO_L24N: U14.P16 (IO_L24N_T3_34); also elsewhere on the board
IO_L24_35_SPI_D0: U14.C20 (IO_L1P_T0_AD0P_35); also elsewhere on the board
IO_L24_35_SPI_DI: U14.B20 (IO_L1N_T0_AD0N_35); also elsewhere on the board
JTAG_BOOT: RA18.2; also elsewhere on the board
MAC_MDIO: U14.C11 (PS_MIO53_501); also elsewhere on the board
unnamed: D3.2 (A), RA28.2
unnamed: D3.1 (K), Q3.3 (D)
unnamed: D4.2 (A), RA29.2
unnamed: D4.1 (K), Q4.3 (D)
unnamed: R40.1, U14.R10 (INIT_B_0)
unnamed: R41.1, U14.L6 (PROGRAM_B_0)
unnamed: R42.2, R43.1, U14.K9 (VP_0)
unnamed: R38.1, U14.G5 (PS_DDR_VRN_502)
unnamed: R37.1, U14.H5 (PS_DDR_VRP_502)
unnamed: RA19.1, U14.E7 (PS_CLK_500)
unnamed: RA21.1, U14.D8 (PS_MIO7_500)
unnamed: RA22.1, U14.D5 (PS_MIO8_500)
unnamed: RA20.1, U14.C5 (PS_MIO14_500)
unnamed: RA24.2, RA26.2, U14.E11 (PS_MIO_VREF_501)
unnamed: RA25.1, U14.B10 (PS_SRST_B_501)
unnamed: R47.1, U18.L8 (ZQ0)
unnamed: C148.1, U21.9 (CAP)
unnamed: C149.1, U21.27 (XIN32), Y3.1
unnamed: C150.1, U21.26 (XOUT32), Y3.2
PHY_RXCLK: U14.B17 (PS_MIO22_501); also elsewhere on the board
PHY_RXD0: U14.D11 (PS_MIO23_501); also elsewhere on the board
PHY_RXD1: U14.A16 (PS_MIO24_501); also elsewhere on the board
PHY_RXD2: U14.F15 (PS_MIO25_501); also elsewhere on the board
PHY_RXD3: U14.A15 (PS_MIO26_501); also elsewhere on the board
PHY_TXCLK: U14.A19 (PS_MIO16_501); also elsewhere on the board
PHY_TXD0: U14.E14 (PS_MIO17_501); also elsewhere on the board
PHY_TXD1: U14.B18 (PS_MIO18_501); also elsewhere on the board
PHY_TXD2: U14.D10 (PS_MIO19_501); also elsewhere on the board
PHY_TXD3: U14.A17 (PS_MIO20_501); also elsewhere on the board
PHY_TXEN: U14.F14 (PS_MIO21_501); also elsewhere on the board
PS: R53.1, U14.J20 (IO_L17P_T2_AD5P_35), U19.2 (PS)
PS_MI00: U14.E6 (PS_MIO0_500); also elsewhere on the board
PS_MI09: U14.B5 (PS_MIO9_500); also elsewhere on the board
PS_MI010: U14.E9 (PS_MIO10_500)
PS_MI011: U14.C6 (PS_MIO11_500); also elsewhere on the board
PS_MI046: U14.D16 (PS_MIO46_501); also elsewhere on the board
PS_MI048: U14.B12 (PS_MIO48_501); also elsewhere on the board
PS_MI049: U14.C12 (PS_MIO49_501); also elsewhere on the board
PS_MI051: U14.B9 (PS_MIO51_501)
PS_MI052: U14.C10 (PS_MIO52_501); also elsewhere on the board
PS_MIO01_500_QSPI0_SS_B: RA12.2, U14.A7 (PS_MIO1_500), U15.1 (CS_)
PS_MIO02_500_QSPI0_IO0: RA15.1, U15.5 (SI/SIO0)
PS_MIO03_500_QSPI0_IO1: RA16.1, U15.2 (SO/SIO1)
PS_MIO04_500_QSPI0_IO2: RA13.1, U15.3 (WP/SIO2)
PS_MIO05_500_QSPI0_IO0: U14.B8 (PS_MIO2_500)
PS_MIO05_500_QSPI0_IO1: U14.D6 (PS_MIO3_500)
PS_MIO05_500_QSPI0_IO2: U14.B7 (PS_MIO4_500)
PS_MIO05_500_QSPI0_IO3: RA17.2, RA18.1, U14.A6 (PS_MIO5_500), U15.7 (NC/SIO3)
PS_MIO06_500_QSPI0_SCLK: RA11.1, U14.A5 (PS_MIO6_500), U15.6 (SCLK)
PS_MIO28_501_USB0_D4: U14.C16 (PS_MIO28_501); also elsewhere on the board
PS_MIO29_501_USB0_DIR: U14.C13 (PS_MIO29_501); also elsewhere on the board
PS_MIO30_501_USB0_STP: U14.C15 (PS_MIO30_501); also elsewhere on the board
PS_MIO31_501_USB0_NXT: U14.E16 (PS_MIO31_501); also elsewhere on the board
PS_MIO32_501_USB0_D0: U14.A14 (PS_MIO32_501); also elsewhere on the board
PS_MIO33_501_USB0_D1: U14.D15 (PS_MIO33_501); also elsewhere on the board
PS_MIO34_501_USB0_D2: U14.A12 (PS_MIO34_501); also elsewhere on the board
PS_MIO35_501_USB0_D3: U14.F12 (PS_MIO35_501); also elsewhere on the board
PS_MIO36_501_USB0_CLK: U14.A11 (PS_MIO36_501); also elsewhere on the board
PS_MIO37_501_USB0_D5: U14.A10 (PS_MIO37_501); also elsewhere on the board
PS_MIO38_501_USB0_D6: U14.E13 (PS_MIO38_501); also elsewhere on the board
PS_MIO39_501_USB0_D7: U14.C18 (PS_MIO39_501); also elsewhere on the board
SCL: U14.U17 (IO_L9N_T1_DQS_34); also elsewhere on the board
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
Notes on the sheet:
256x16bit
Pressure & Temp. Sencor
FBGA96-10X14-A
BNO085 9-Axis Orientation Sensor
